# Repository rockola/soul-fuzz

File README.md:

# soul-fuzz

Soul Fuzz by psychic fx

* 0.1: initial version
* 0.2: added LED, power/stomp connectors, polarity protection

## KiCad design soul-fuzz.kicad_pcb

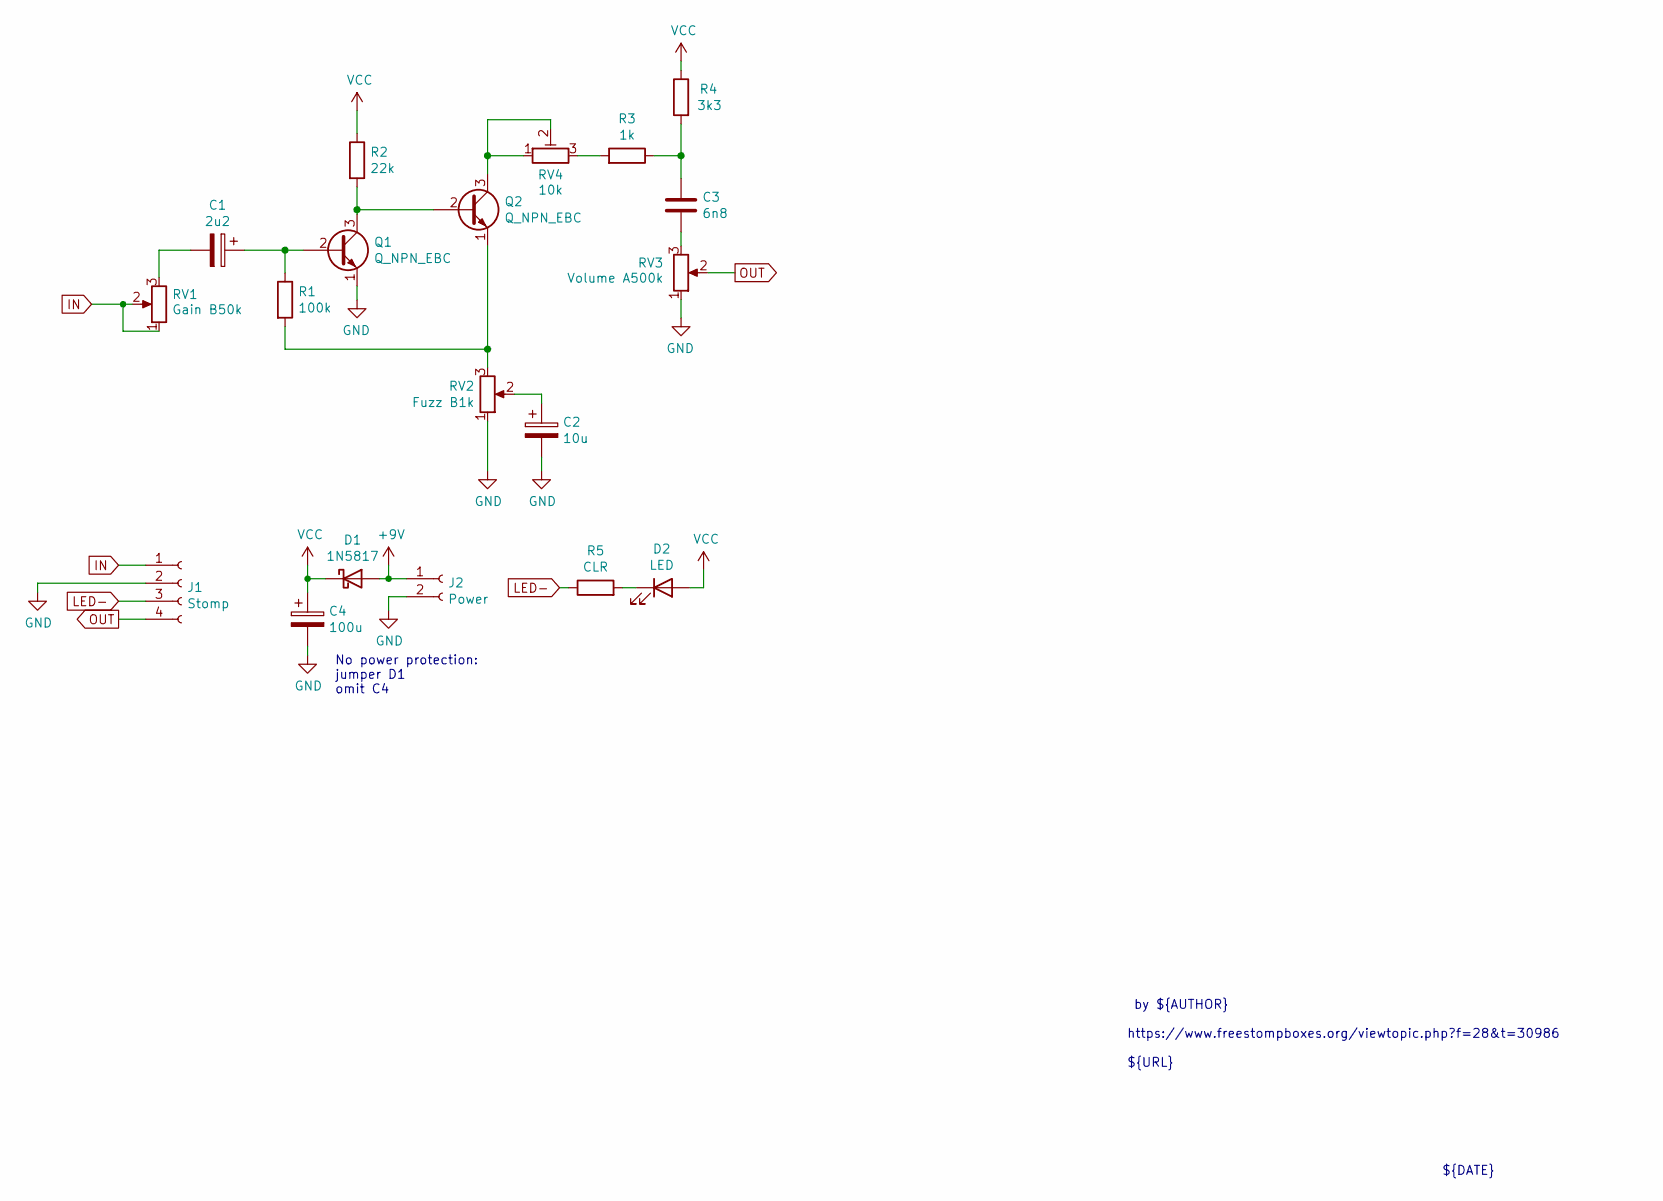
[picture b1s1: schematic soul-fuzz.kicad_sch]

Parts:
C1: 2u2; CP_D5.0_P2.50
C2: 10u; CP_D5.0_P2.50
C3: 6n8; C_Box_7.2_2.5
C4: 100u; CP_D6.3_P2.50
D1: 1N5817; D_DO-41_SOD81_P10.16mm_Horizontal
D2: LED; LED.3mm
J1: Stomp; Stomp_4pin
J2: Power; Power_Header_2pin_TOP
Q1, Q2: Q_NPN_EBC; TO92_EBC
R1: 100k; R_DIN0207
R2: 22k; R_DIN0207
R3: 1k; R_DIN0207
R4: 3k3; R_DIN0207
R5: CLR; R_DIN0207
RV1: Gain B50k; 16MM_B.MOUNT
RV2: Fuzz B1k; 16MM_B.MOUNT
RV3: Volume A500k; 16MM_B.MOUNT
RV4: 10k; TRIM1

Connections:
+9V: D1.2 (A), J2.1
GND: C2.2, C4.2, J1.2, J2.2, Q1.1 (E), RV2.1, RV3.1
IN: J1.1, RV1.1, RV1.2
LED-: J1.3, R5.1
unnamed: C1.1, Q1.2 (B), R1.1
unnamed: C1.2, RV1.3
unnamed: C2.1, RV2.2
unnamed: C3.1, R3.1, R4.2
unnamed: C3.2, RV3.3
unnamed: D2.1 (K), R5.2
unnamed: Q1.3 (C), Q2.2 (B), R2.2
unnamed: Q2.1 (E), R1.2, RV2.3
unnamed: Q2.3 (C), RV4.1, RV4.2
unnamed: R3.2, RV4.3
OUT: J1.4, RV3.2
VCC: C4.1, D1.1 (K), D2.2 (A), R2.1, R4.1

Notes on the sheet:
No power protection: jumper D1 omit C4
${TITLE} by ${AUTHOR} https://www.freestompboxes.org/viewtopic.php?f=28&t=30986 ${URL}
${TITLE}
${DATE}
${REVISION}

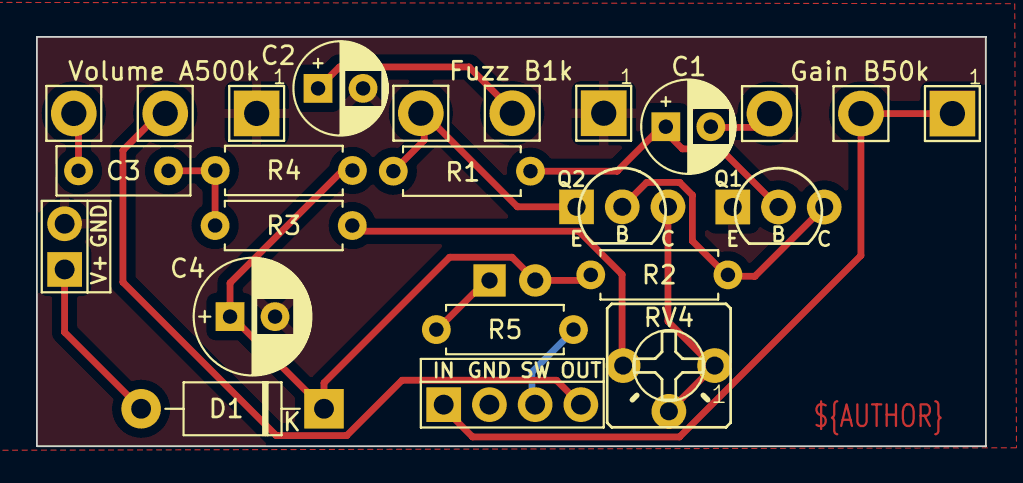
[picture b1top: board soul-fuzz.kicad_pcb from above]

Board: 2 copper layers, 52.7 x 22.7 mm, 19 parts (1 on the bottom side), 16 nets.

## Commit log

2020-11-17 v0.2: initial github version
2020-11-17 v0.2 schematic added for posterity
